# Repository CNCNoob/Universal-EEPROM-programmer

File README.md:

# Universal-EEPROM-Programmer 

Marvellouse EEPROM programming device that will support many EEPROMs and some EPROMs

main Arduino shield with 28pin molex connector which connects to user specific boards.

Created and programmed using: [KiCad](kicad-pcb.org/), [Aduino](arduino.cc) and [processing](https://processing.org/)

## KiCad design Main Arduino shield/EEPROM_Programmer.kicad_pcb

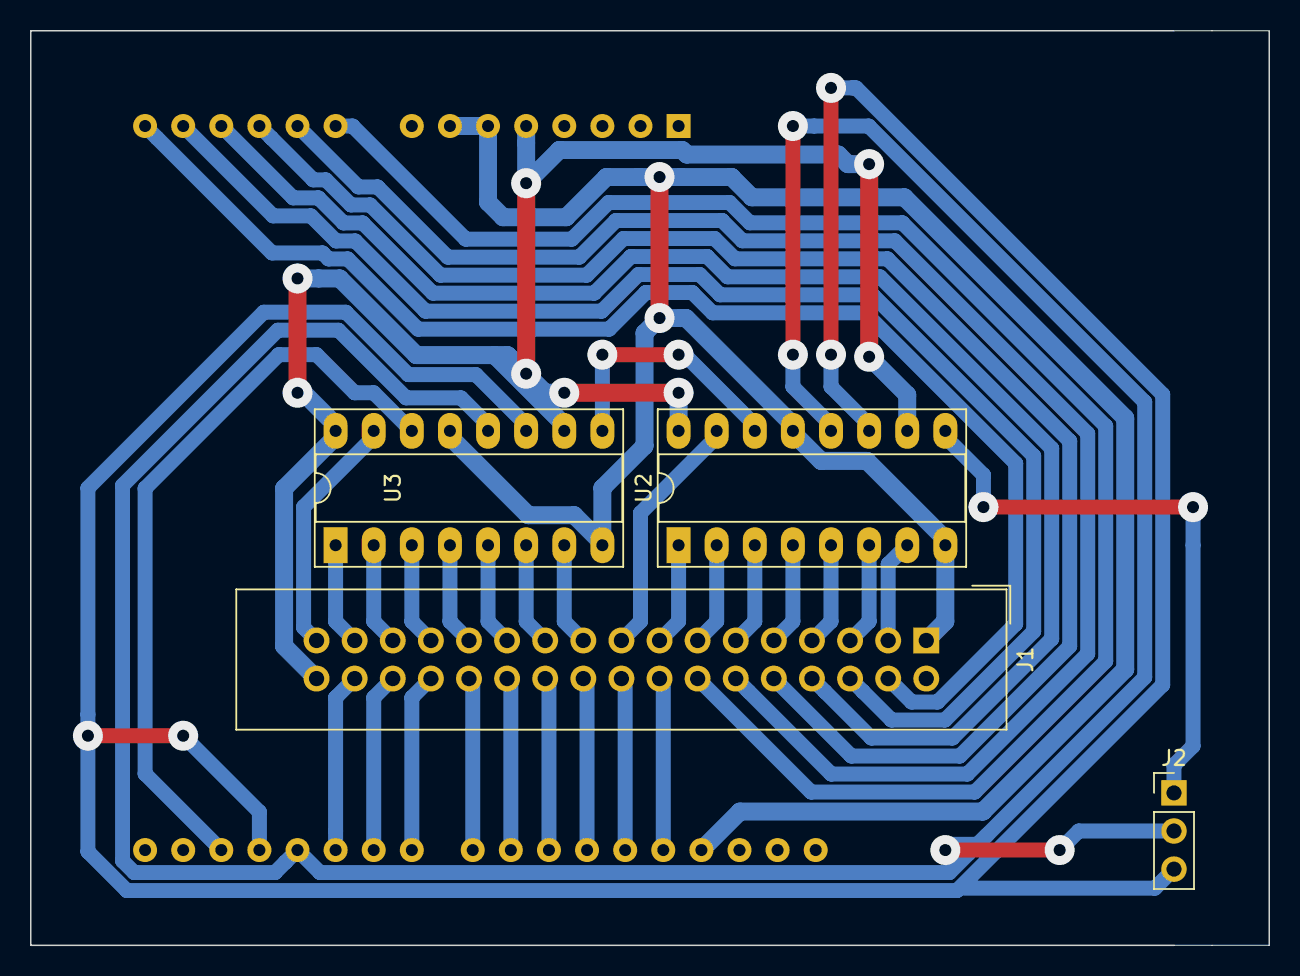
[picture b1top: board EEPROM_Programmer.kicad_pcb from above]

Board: 2 copper layers, 82.6 x 61.0 mm, 5 parts (0 on the bottom side), 38 nets.

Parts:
J1: Conn_02x17_Odd_Even; IDC-Header_2x17_P2.54mm_Vertical
J2: Conn_01x03; PinHeader_1x03_P2.54mm_Vertical
U1: Arduino_UNO_R3
U2, U3: 74HC595; DIP-16_W7.62mm_Socket_LongPads

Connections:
+5V: J1.34, U1.5, U2.10, U2.16, U3.10, U3.16
/A0: J1.33, U3.15
/A1: J1.31, U3.1
/A2: J1.29, U3.2
/A3: J1.27, U3.3
/A4: J1.25, U3.4
/A5: J1.23, U3.5
/A6: J1.21, U3.6
/A7: J1.19, U3.7
/A8: J1.17, U2.15
/A9: J1.15, U2.1
/A10: J1.13, U2.2
/A11: J1.11, U2.3
/A12: J1.9, U2.4
/A13: J1.7, U2.5
/A14: J1.5, U2.6
/A15: J1.3, U2.7
/D0: J1.32, U1.20
/D1: J1.30, U1.21
/D2: J1.28, U1.22
/D3: J1.26, U1.23
/D4: J1.24, U1.24
/D5: J1.22, U1.25
/D6: J1.20, U1.26
/D7: J1.18, U1.27
/OE: J1.16, U1.28
/S0: J1.14, U1.9
/S1: J1.12, U1.10
/S2: J1.10, U1.11
/S3: J1.8, U1.12
/SCL: J1.4, U1.14
/SDA: J1.6, U1.13
Earth: J1.1, U1.6, U1.7, U1.29, U2.8, U2.13, U3.8, U3.13
unnamed: J2.1, U2.9
unnamed: J2.2, U1.19, U2.12, U3.12
unnamed: J2.3, U1.18, U2.11, U3.11
unnamed: U1.17, U3.14
unnamed: U2.14, U3.9

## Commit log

2019-06-23 Create LICENSE
2019-06-23 Set theme jekyll-theme-cayman
2019-06-23 Create schematic
2019-06-23 uploaded schematic file
2019-06-23 Edited design specifications
2019-06-24 Add main Arduino shield Gerber files
2019-06-24 added folder
2019-06-24 Added main shield sch/pcb
2019-06-26 deleted 34Pin Connector pinouts
2019-06-29 Added 28C256 extension board
2019-06-29 deleted second liscence and readme
2019-06-29 added schematic pdf's
2019-06-29 adding used programs
